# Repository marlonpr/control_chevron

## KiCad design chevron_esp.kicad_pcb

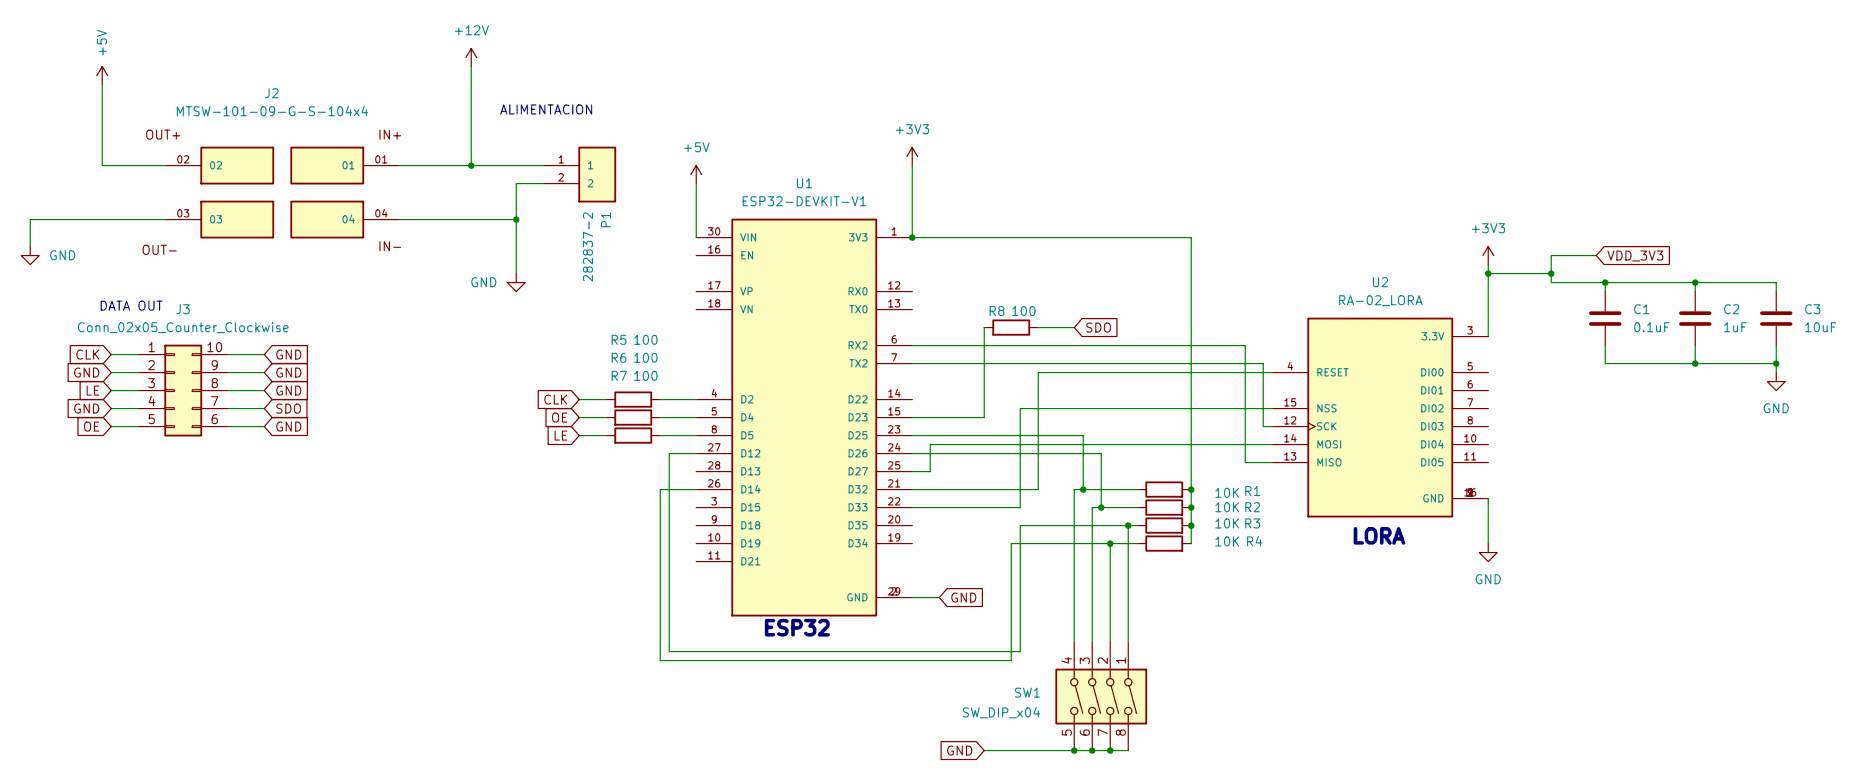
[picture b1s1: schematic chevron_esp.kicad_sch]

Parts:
C1: 0.1uF; C_0603_1608Metric_Pad1.08x0.95mm_HandSolder
C2: 1uF; C_1206_3216Metric_Pad1.33x1.80mm_HandSolder
C3: 10uF; C_0805_2012Metric_Pad1.18x1.45mm_HandSolder
J2: MTSW-101-09-G-S-104x4; SAMTEC_MTSW-101-09-G-S-104x4
J3: Conn_02x05_Counter_Clockwise; IDC-Header_2x05_P2.54mm_Vertical
P1: 282837-2; PinHeader_1x02_P2.54mm_Vertical; PARTREV G3
R1, R2, R3, R4: 10K; R_1206_3216Metric_Pad1.30x1.75mm_HandSolder
R5, R6, R7, R8: 100; R_1206_3216Metric_Pad1.30x1.75mm_HandSolder
SW1: SW_DIP_x04; SW_DIP_SPSTx04_Slide_6.7x11.72mm_W7.62mm_P2.54mm_LowProfile
U1: ESP32-DEVKIT-V1; MODULE_ESP32_DEVKIT_V1; PARTREV N/A
U2: RA-02_LORA; TE_826629-8x2

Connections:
+5V: J2.02, U1.30 (VIN)
+12V: J2.01, P1.1
CLK: J3.1, R5.2
GND: C1.2, C2.2, C3.2, J2.03, J2.04, J3.2, J3.4, J3.6, J3.8, J3.9, J3.10, P1.2, SW1.5, SW1.6, SW1.7, SW1.8, U1.2 (GND), U1.29 (GND), U2.1 (GND), U2.2 (GND), U2.9 (GND), U2.16 (GND)
LE: J3.3, R7.2
unnamed: R5.1, U1.4 (D2)
unnamed: R6.1, U1.5 (D4)
unnamed: R7.1, U1.8 (D5)
unnamed: R3.1, SW1.1, U1.27 (D12)
unnamed: R4.1, SW1.2, U1.26 (D14)
unnamed: R8.2, U1.15 (D23)
unnamed: R1.1, SW1.4, U1.23 (D25)
unnamed: R2.1, SW1.3, U1.24 (D26)
unnamed: U1.25 (D27), U2.14 (MOSI)
unnamed: U1.21 (D32), U2.4 (RESET)
unnamed: U1.22 (D33), U2.15 (NSS)
unnamed: U1.6 (RX2), U2.13 (MISO)
unnamed: U1.7 (TX2), U2.12 (SCK)
OE: J3.5, R6.2
SDO: J3.7, R8.1
VDD_3V3: C1.1, C2.1, C3.1, R1.2, R2.2, R3.2, R4.2, U1.1 (3V3), U2.3 (3.3V)

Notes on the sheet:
LORA
ESP32
ALIMENTACION
DATA OUT

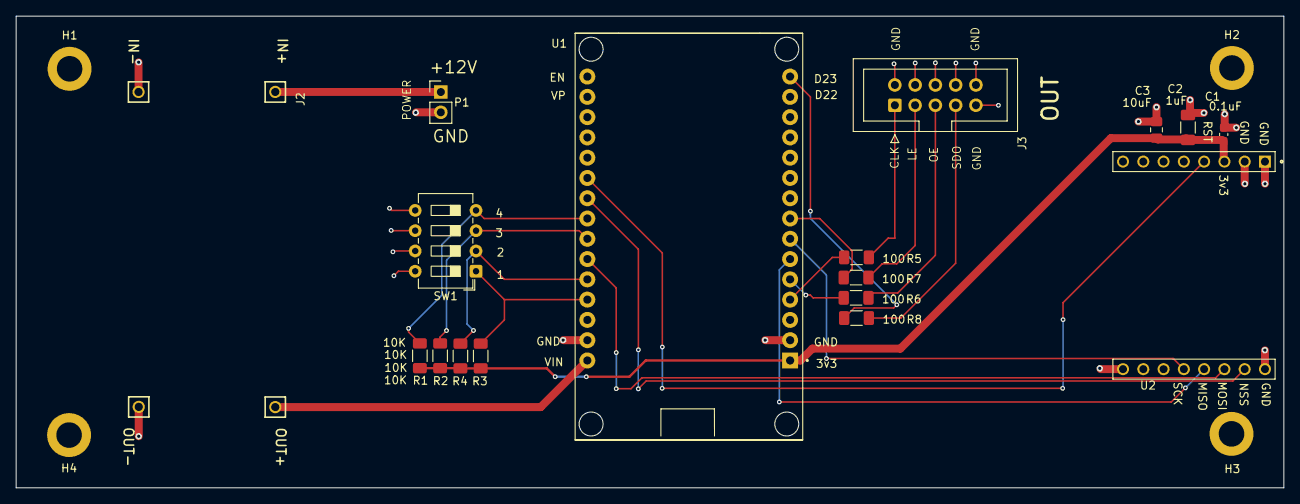
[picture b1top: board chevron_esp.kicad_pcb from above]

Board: 2 copper layers, 158.8 x 59.1 mm, 21 parts (0 on the bottom side), 21 nets.

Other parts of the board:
H1, H2, H3, H4: 3.2mm_M3_TH

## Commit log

2025-09-23 chevron esp v1.0
2025-09-23 chevron esp v1.1
2025-09-24 chevron esp v1.2
2025-10-14 chevron esp v1.3
2026-05-05 Stop tracking backup files
2026-05-05 untrack cache
2026-05-05 v1 ok
2026-05-06 cleanup tracks and vias
